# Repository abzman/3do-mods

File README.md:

# 3do-mods
repository of documentation for 3do modifications

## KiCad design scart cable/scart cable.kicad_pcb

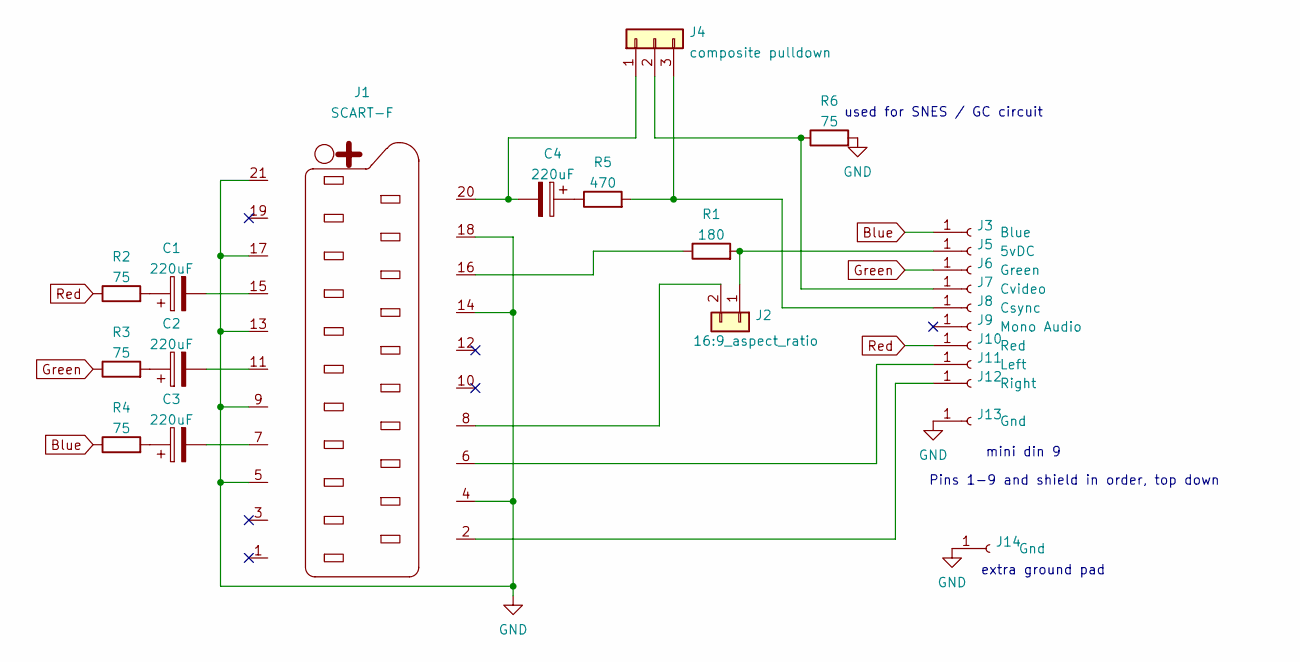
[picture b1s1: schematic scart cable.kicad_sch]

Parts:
C1, C2, C3, C4: 220uF; CP_Elec_6.3x5.2
J1: SCART-F; edge mount SCART
J2: 16:9_aspect_ratio; SolderJumper-2_P1.3mm_Bridged_RoundedPad1.0x1.5mm
J3: Blue; raw pad to splder to
J4: composite pulldown; SolderJumper-3_P1.3mm_Open_RoundedPad1.0x1.5mm
J5: 5vDC; raw pad to splder to
J6: Green; raw pad to splder to
J7: Cvideo; raw pad to splder to
J8: Csync; raw pad to splder to
J9: Mono Audio; raw pad to splder to
J10: Red; raw pad to splder to
J11: Left; raw pad to splder to
J12: Right; raw pad to splder to
J13, J14: Gnd; raw pad to splder to
R1: 180; R_0603_1608Metric
R2, R3, R4, R6: 75; R_0603_1608Metric
R5: 470; R_0603_1608Metric

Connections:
Blue: J3.1, R4.1
GND: J1.4, J1.5, J1.9, J1.13, J1.14, J1.17, J1.18, J1.21, J13.1, J14.1, R6.2
Green: J6.1, R3.1
unnamed: C1.1, R2.2
unnamed: C1.2, J1.15
unnamed: C2.1, R3.2
unnamed: C2.2, J1.11
unnamed: C3.1, R4.2
unnamed: C3.2, J1.7
unnamed: C4.1, R5.1
unnamed: C4.2, J1.20, J4.1
unnamed: J1.2, J12.1
unnamed: J1.6, J11.1
unnamed: J1.8, J2.2
unnamed: J1.16, R1.1
unnamed: J2.1, J5.1, R1.2
unnamed: J4.2, J7.1, R6.1
unnamed: J4.3, J8.1, R5.2
Red: J10.1, R2.1

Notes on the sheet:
extra ground pad
Pins 1-9 and shield in order, top down
mini din 9
used for SNES / GC circuit

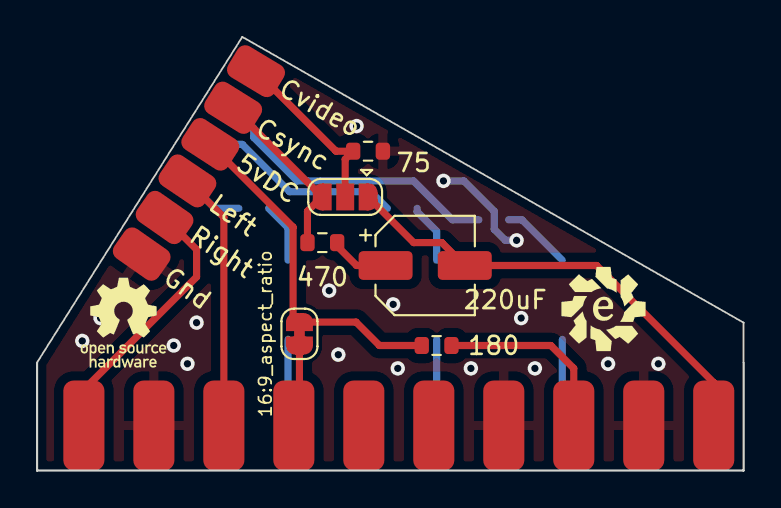
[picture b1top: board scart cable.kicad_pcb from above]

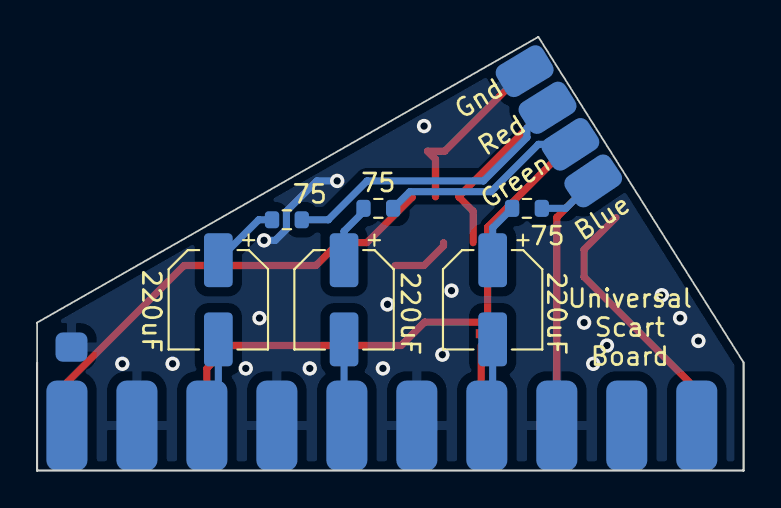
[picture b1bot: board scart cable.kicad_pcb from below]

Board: 2 copper layers, 39.2 x 24.1 mm, 23 parts (10 on the bottom side), 19 nets.

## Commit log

2022-12-09 updated gitignore
2022-12-12 added annotated schematics, original schematics, and datasheet for replacement chip
2022-12-23 added scart cable pinout
2022-12-25 replaced datasheet
2022-12-31 made scart cable board
2022-12-31 added gerbers for scart cable end
2023-01-06 added docs
2024-01-18 added images
